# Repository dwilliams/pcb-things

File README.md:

# pcb-things
A place to keep all of the PCB things that don't fit in a project

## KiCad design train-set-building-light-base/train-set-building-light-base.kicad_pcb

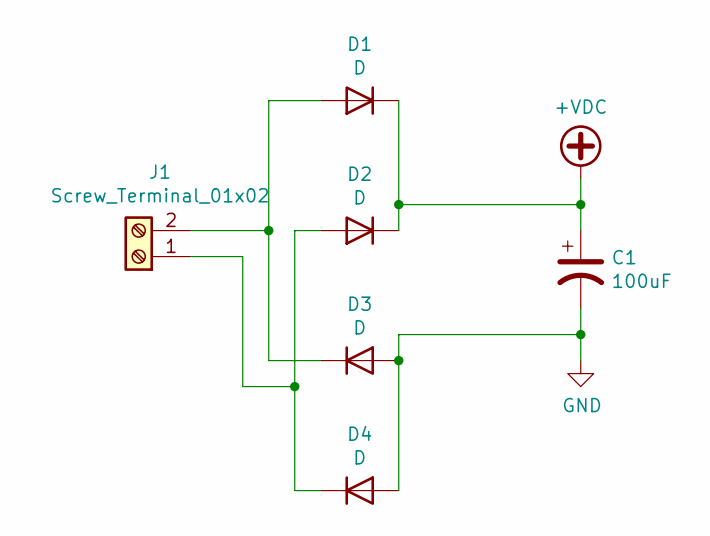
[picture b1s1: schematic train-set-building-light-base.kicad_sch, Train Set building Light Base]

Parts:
C1: 100uF; CP_Elec_8x5.4
D1, D2, D3, D4: D; D_SMA-SMB_Universal_Handsoldering
J1: Screw_Terminal_01x02; PhoenixContact_MCV_1,5_2-G-5.08_1x02_P5.08mm_Vertical

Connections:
+VDC: C1.1, D1.1 (K), D2.1 (K)
GND: C1.2, D3.2 (A), D4.2 (A)
unnamed: D1.2 (A), D3.1 (K), J1.2
unnamed: D2.2 (A), D4.1 (K), J1.1

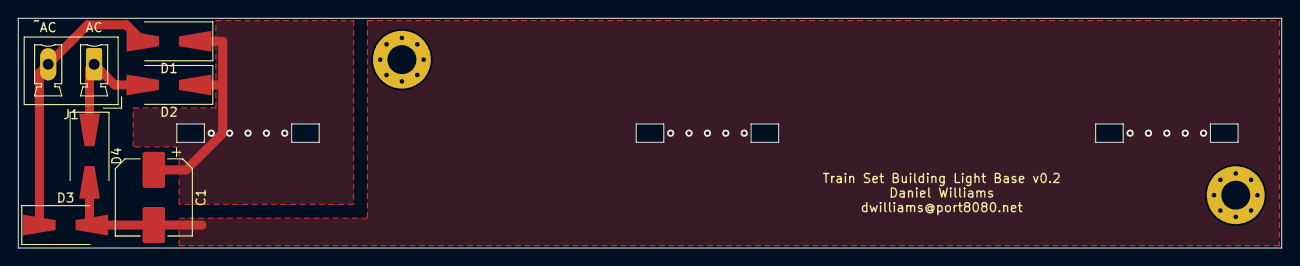
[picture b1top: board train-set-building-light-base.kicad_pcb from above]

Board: 2 copper layers, 139.7 x 25.4 mm, 6 parts (0 on the bottom side), 4 nets.

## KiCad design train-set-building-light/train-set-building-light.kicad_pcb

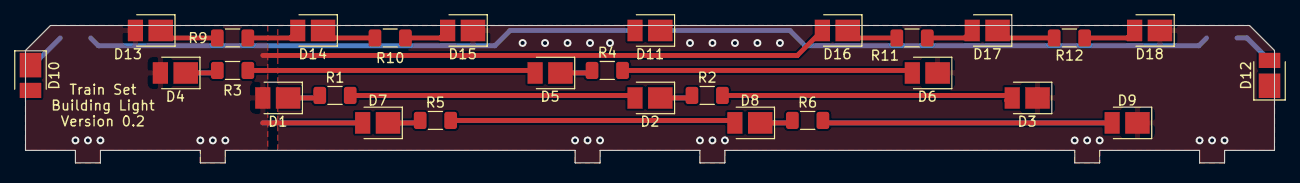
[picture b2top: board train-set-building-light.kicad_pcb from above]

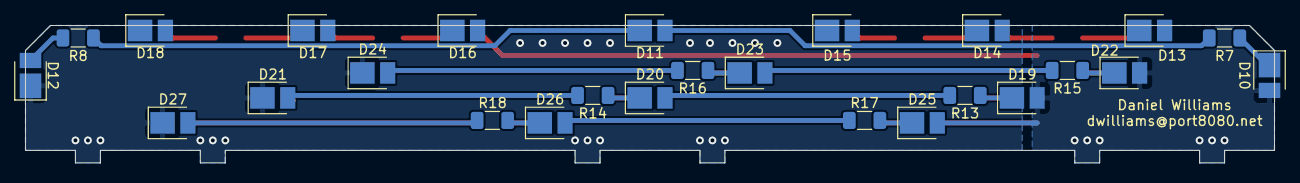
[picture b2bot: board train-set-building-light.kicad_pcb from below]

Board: 2 copper layers, 127.0 x 14.0 mm, 54 parts (26 on the bottom side), 38 nets.

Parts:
D1, D2, D3, D4, D5, D6, D7, D8, D9, D10, D10#2, D11, D11#2, D12, D12#2, D13, D13#2, D14, D14#2, D15, D15#2, D16, D16#2, D17, D17#2, D18, D18#2, D19, D20, D21, D22, D23, D24, D25, D26, D27: LED; LED_PLCC_2835_Handsoldering
R1, R2, R3, R4, R5, R6, R7, R8, R9, R10, R11, R12, R13, R14, R15, R16, R17, R18: 150; R_1206_3216Metric_Pad1.30x1.75mm_HandSolder

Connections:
+VDC: D1.2, D4.2, D7.2, D10#2.2, D13.2, D16.2, D19.2, D22.2, D25.2
GND: D3.1, D6.1, D9.1, D12#2.1, D15.1, D18.1, D21.1, D24.1, D27.1
unnamed: D1.1, R1.1
unnamed: D2.1, R2.1
unnamed: D2.2, R1.2
unnamed: D3.2, R2.2
unnamed: D4.1, R3.1
unnamed: D5.1, R4.1
unnamed: D5.2, R3.2
unnamed: D6.2, R4.2
unnamed: D7.1, R5.1
unnamed: D8.1, R6.1
unnamed: D8.2, R5.2
unnamed: D9.2, R6.2
unnamed: D10#2.1, R7.1
unnamed: D11#2.1, R8.1
unnamed: D11#2.2, R7.2
unnamed: D12#2.2, R8.2
unnamed: D13.1, R9.1
unnamed: D14.1, R10.1
unnamed: D14.2, R9.2
unnamed: D15.2, R10.2
unnamed: D16.1, R11.1
unnamed: D17.1, R12.1
unnamed: D17.2, R11.2
unnamed: D18.2, R12.2
unnamed: D19.1, R13.1
unnamed: D20.1, R14.1
unnamed: D20.2, R13.2
unnamed: D21.2, R14.2
unnamed: D22.1, R15.1
unnamed: D23.1, R16.1
unnamed: D23.2, R15.2
unnamed: D24.2, R16.2
unnamed: D25.1, R17.1
unnamed: D26.1, R18.1
unnamed: D26.2, R17.2
unnamed: D27.2, R18.2

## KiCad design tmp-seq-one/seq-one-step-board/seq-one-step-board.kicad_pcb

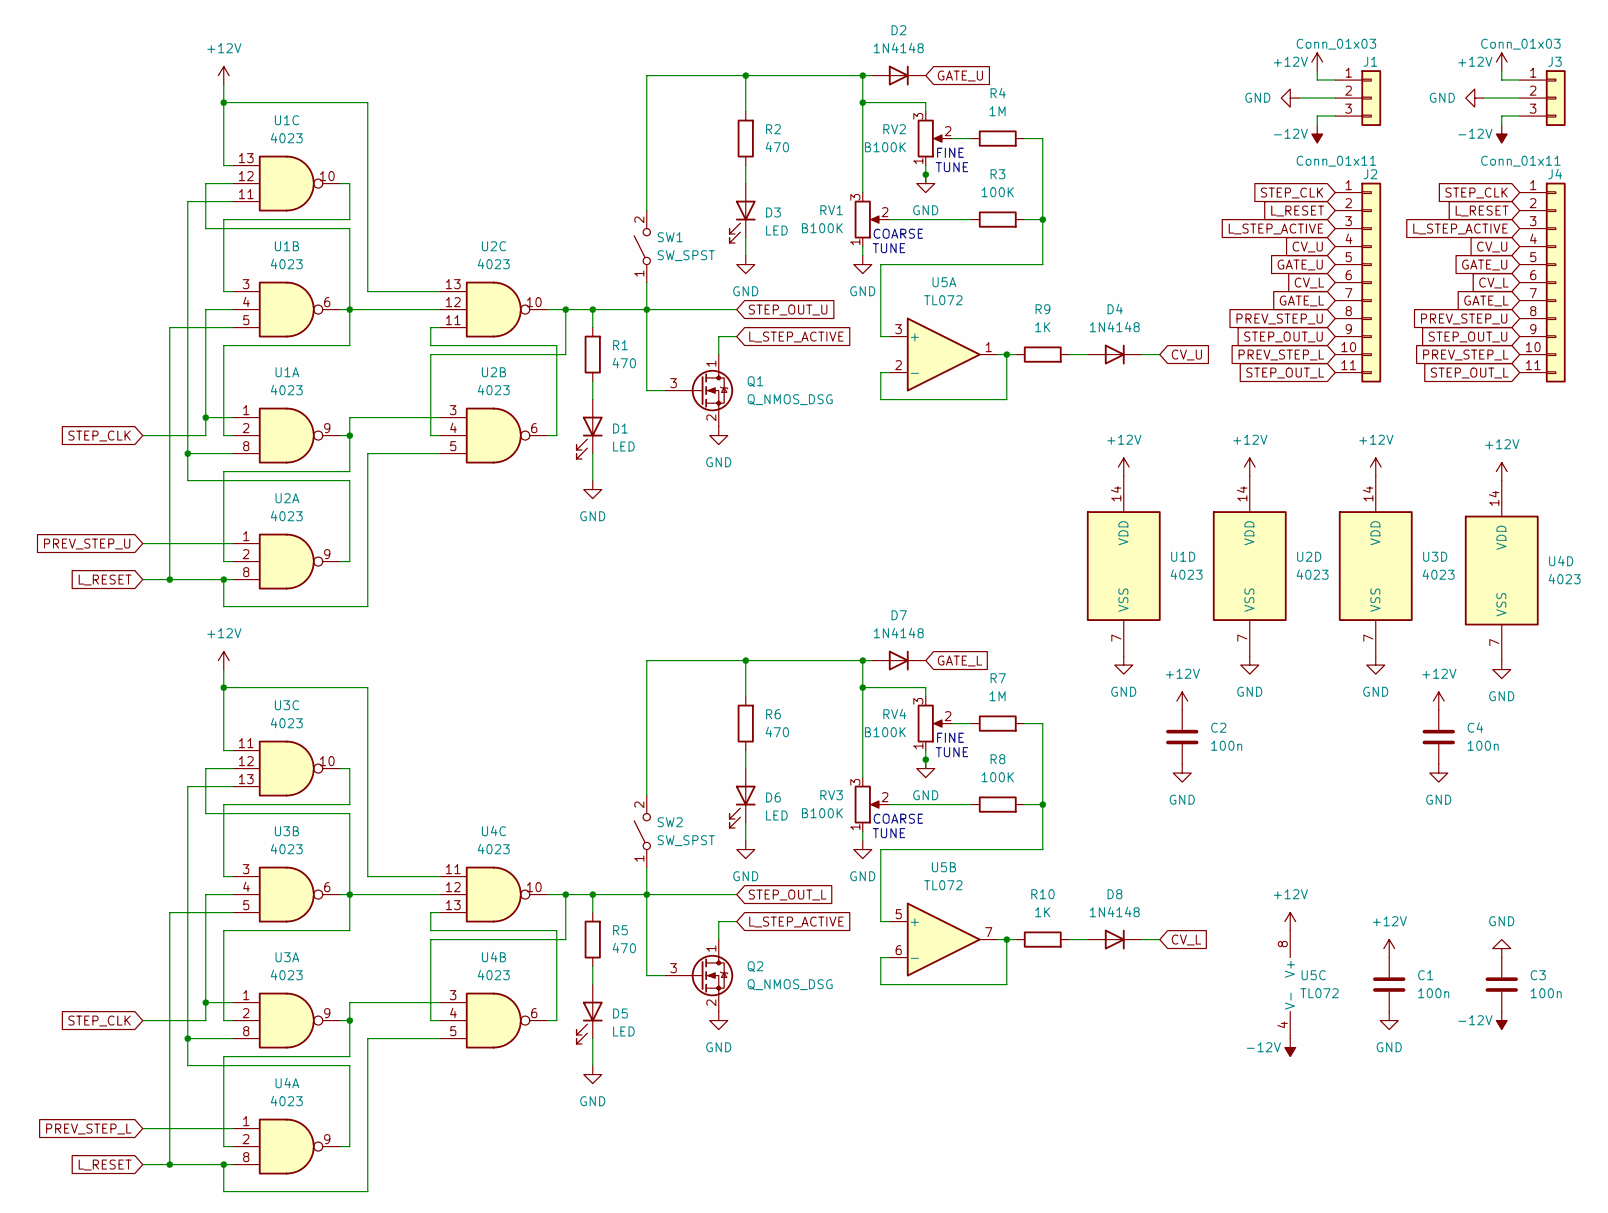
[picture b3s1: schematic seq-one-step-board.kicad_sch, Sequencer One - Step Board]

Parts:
C1, C2, C3, C4: 100n; C_Disc_D5.1mm_W3.2mm_P5.00mm
D1, D3, D5, D6: LED; LED_D3.0mm
D2, D4, D7, D8: 1N4148; D_DO-35_SOD27_P7.62mm_Horizontal
J1, J3: Conn_01x03; PinHeader_1x03_P2.54mm_Vertical
J2, J4: Conn_01x11; PinHeader_1x11_P2.54mm_Vertical
Q1, Q2: Q_NMOS_DSG; TO-92_HandSolder
R1, R2, R5, R6: 470; R_Axial_DIN0204_L3.6mm_D1.6mm_P7.62mm_Horizontal
R3, R8: 100K; R_Axial_DIN0204_L3.6mm_D1.6mm_P7.62mm_Horizontal
R4, R7: 1M; R_Axial_DIN0204_L3.6mm_D1.6mm_P7.62mm_Horizontal
R9, R10: 1K; R_Axial_DIN0204_L3.6mm_D1.6mm_P7.62mm_Horizontal
RV1, RV2, RV3, RV4: B100K; Potentiometer_Piher_T-16H_Single_Horizontal
SW1, SW2: SW_SPST; PinHeader_1x02_P2.54mm_Vertical
U1, U2, U3, U4: 4023; DIP-14_W7.62mm_Socket_LongPads
U5: TL072; DIP-8_W7.62mm_Socket_LongPads

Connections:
+12V: C1.1, C2.1, C4.1, J1.1, J3.1, U1.13, U1.14 (VDD), U2.13, U2.14 (VDD), U3.11, U3.14 (VDD), U4.11, U4.14 (VDD), U5.8 (V+)
-12V: C3.2, J1.3, J3.3, U5.4 (V-)
CV_L: D8.1 (K), J2.6, J4.6
CV_U: D4.1 (K), J2.4, J4.4
GATE_L: D7.1 (K), J2.7, J4.7
GATE_U: D2.1 (K), J2.5, J4.5
GND: C1.2, C2.2, C3.1, C4.2, D1.1 (K), D3.1 (K), D5.1 (K), D6.1 (K), J1.2, J3.2, Q1.2 (S), Q2.2 (S), RV1.1, RV2.1, RV3.1, RV4.1, U1.7 (VSS), U2.7 (VSS), U3.7 (VSS), U4.7 (VSS)
L_RESET: J2.2, J4.2, U1.5, U2.5, U2.8, U3.5, U4.5, U4.8
L_STEP_ACTIVE: J2.3, J4.3, Q1.1 (D), Q2.1 (D)
unnamed: D1.2 (A), R1.1
unnamed: D2.2 (A), R2.2, RV1.3, RV2.3, SW1.2 (B)
unnamed: D3.2 (A), R2.1
unnamed: D4.2 (A), R9.2
unnamed: D5.2 (A), R5.1
unnamed: D6.2 (A), R6.1
unnamed: D7.2 (A), R6.2, RV3.3, RV4.3, SW2.2 (B)
unnamed: D8.2 (A), R10.2
unnamed: R3.1, RV1.2
unnamed: R3.2, R4.2, U5.3 (+)
unnamed: R4.1, RV2.2
unnamed: R7.1, RV4.2
unnamed: R7.2, R8.2, U5.5 (+)
unnamed: R8.1, RV3.2
unnamed: R9.1, U5.1, U5.2 (-)
unnamed: R10.1, U5.6 (-), U5.7
unnamed: U1.9, U2.2, U2.3
unnamed: U1.3, U1.10
unnamed: U1.8, U1.11, U2.9
unnamed: U1.2, U1.6, U1.12, U2.12
unnamed: U2.6, U2.11
unnamed: U3.9, U4.2, U4.3
unnamed: U3.3, U3.10
unnamed: U3.2, U3.6, U3.12, U4.12
unnamed: U3.8, U3.13, U4.9
unnamed: U4.6, U4.13
PREV_STEP_L: J2.10, J4.10, U4.1
PREV_STEP_U: J2.8, J4.8, U2.1
STEP_CLK: J2.1, J4.1, U1.1, U1.4, U3.1, U3.4
STEP_OUT_L: J2.11, J4.11, Q2.3 (G), R5.2, SW2.1 (A), U4.4, U4.10
STEP_OUT_U: J2.9, J4.9, Q1.3 (G), R1.2, SW1.1 (A), U2.4, U2.10

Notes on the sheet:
COARSE TUNE
FINE TUNE

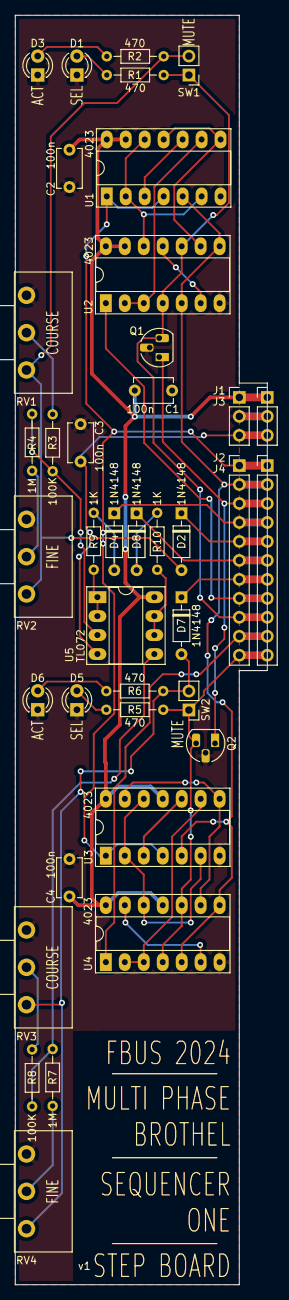
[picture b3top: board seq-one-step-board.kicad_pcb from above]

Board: 2 copper layers, 33.8 x 170.0 mm, 39 parts (0 on the bottom side), 40 nets.

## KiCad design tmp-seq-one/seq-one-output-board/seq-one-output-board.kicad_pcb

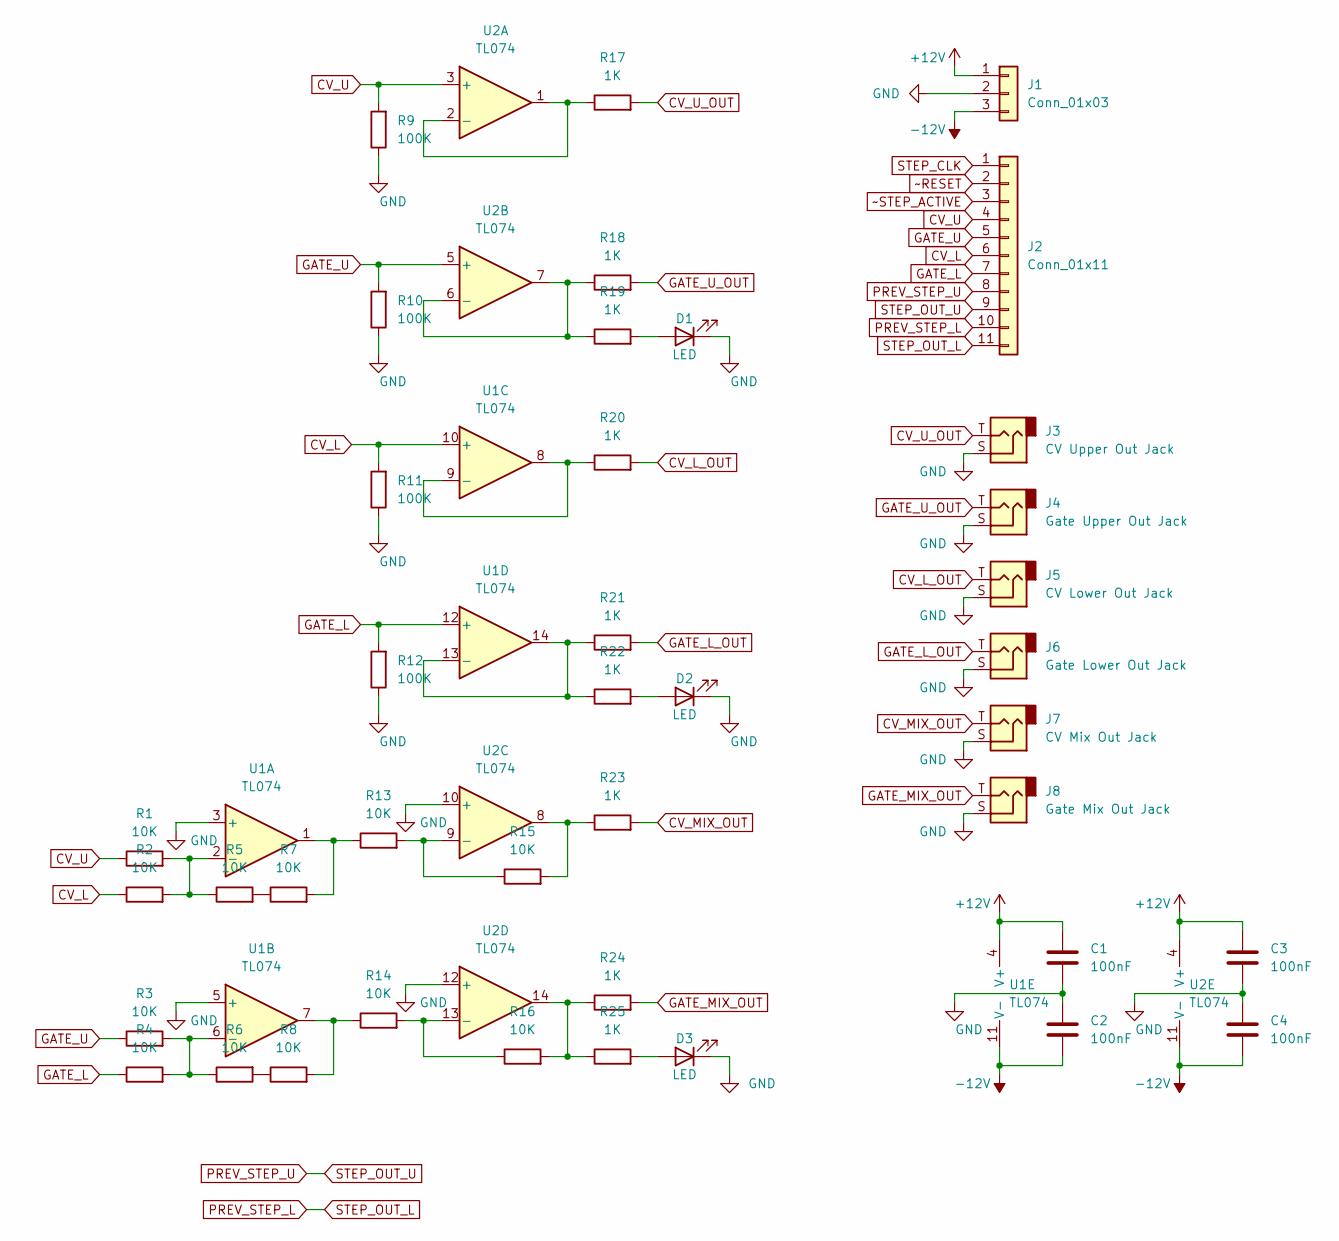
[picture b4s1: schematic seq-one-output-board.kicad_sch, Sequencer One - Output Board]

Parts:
C1, C2, C3, C4: 100nF; C_Disc_D5.1mm_W3.2mm_P5.00mm
D1, D2, D3: LED; LED_D5.0mm
J1: Conn_01x03; PinHeader_1x03_P2.54mm_Vertical
J2: Conn_01x11; PinHeader_1x11_P2.54mm_Vertical
J3: CV Upper Out Jack; Jack_6.35mm_Neutrik_NRJ6HM-1-PRE_Horizontal
J4: Gate Upper Out Jack; Jack_6.35mm_Neutrik_NRJ6HM-1-PRE_Horizontal
J5: CV Lower Out Jack; Jack_6.35mm_Neutrik_NRJ6HM-1-PRE_Horizontal
J6: Gate Lower Out Jack; Jack_6.35mm_Neutrik_NRJ6HM-1-PRE_Horizontal
J7: CV Mix Out Jack; Jack_6.35mm_Neutrik_NRJ6HM-1-PRE_Horizontal
J8: Gate Mix Out Jack; Jack_6.35mm_Neutrik_NRJ6HM-1-PRE_Horizontal
R1, R2, R3, R4, R5, R6, R7, R8, R13, R14, R15, R16: 10K; R_Axial_DIN0204_L3.6mm_D1.6mm_P7.62mm_Horizontal
R9, R10, R11, R12: 100K; R_Axial_DIN0204_L3.6mm_D1.6mm_P7.62mm_Horizontal
R17, R18, R19, R20, R21, R22, R23, R24, R25: 1K; R_Axial_DIN0204_L3.6mm_D1.6mm_P7.62mm_Horizontal
U1, U2: TL074; DIP-14_W7.62mm_Socket_LongPads

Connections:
+12V: C1.1, C3.1, J1.1, U1.4 (V+), U2.4 (V+)
-12V: C2.2, C4.2, J1.3, U1.11 (V-), U2.11 (V-)
CV_L: J2.6, R2.1, R11.2, U1.10 (+)
CV_L_OUT: J5.T, R20.2
CV_MIX_OUT: J7.T, R23.2
CV_U: J2.4, R1.1, R9.2, U2.3 (+)
CV_U_OUT: J3.T, R17.2
GATE_L: J2.7, R4.1, R12.2, U1.12 (+)
GATE_L_OUT: J6.T, R21.2
GATE_MIX_OUT: J8.T, R24.2
GATE_U: J2.5, R3.1, R10.2, U2.5 (+)
GATE_U_OUT: J4.T, R18.2
GND: C1.2, C2.1, C3.2, C4.1, D1.1 (K), D2.1 (K), D3.1 (K), J1.2, J3.S, J4.S, J5.S, J6.S, J7.S, J8.S, R9.1, R10.1, R11.1, R12.1, U1.3 (+), U1.5 (+), U2.10 (+), U2.12 (+)
unnamed: D1.2 (A), R19.2
unnamed: D2.2 (A), R22.2
unnamed: D3.2 (A), R25.2
unnamed: R1.2, R2.2, R5.1, U1.2 (-)
unnamed: R3.2, R4.2, R6.1, U1.6 (-)
unnamed: R5.2, R7.1
unnamed: R6.2, R8.1
unnamed: R7.2, R13.1, U1.1
unnamed: R13.2, R15.1, U2.9 (-)
unnamed: R8.2, R14.1, U1.7
unnamed: R14.2, R16.1, U2.13 (-)
unnamed: R15.2, R23.1, U2.8
unnamed: R16.2, R24.1, R25.1, U2.14
unnamed: R17.1, U2.1, U2.2 (-)
unnamed: R18.1, R19.1, U2.6 (-), U2.7
unnamed: R20.1, U1.8, U1.9 (-)
unnamed: R21.1, R22.1, U1.13 (-), U1.14
PREV_STEP_L: J2.10, J2.11
PREV_STEP_U: J2.8, J2.9
STEP_CLK: J2.1
~RESET: J2.2
~STEP_ACTIVE: J2.3

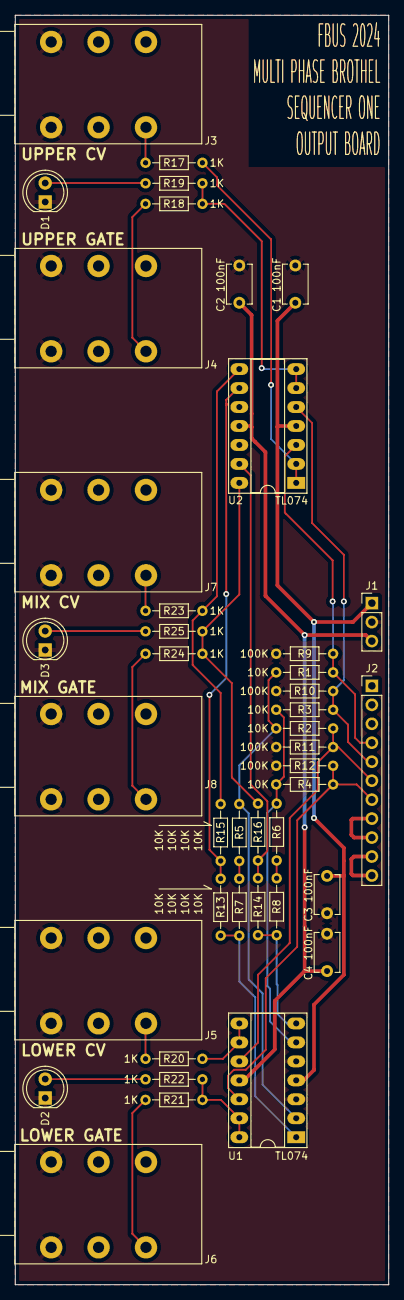
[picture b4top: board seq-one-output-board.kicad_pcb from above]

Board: 2 copper layers, 50.0 x 170.0 mm, 42 parts (0 on the bottom side), 32 nets.

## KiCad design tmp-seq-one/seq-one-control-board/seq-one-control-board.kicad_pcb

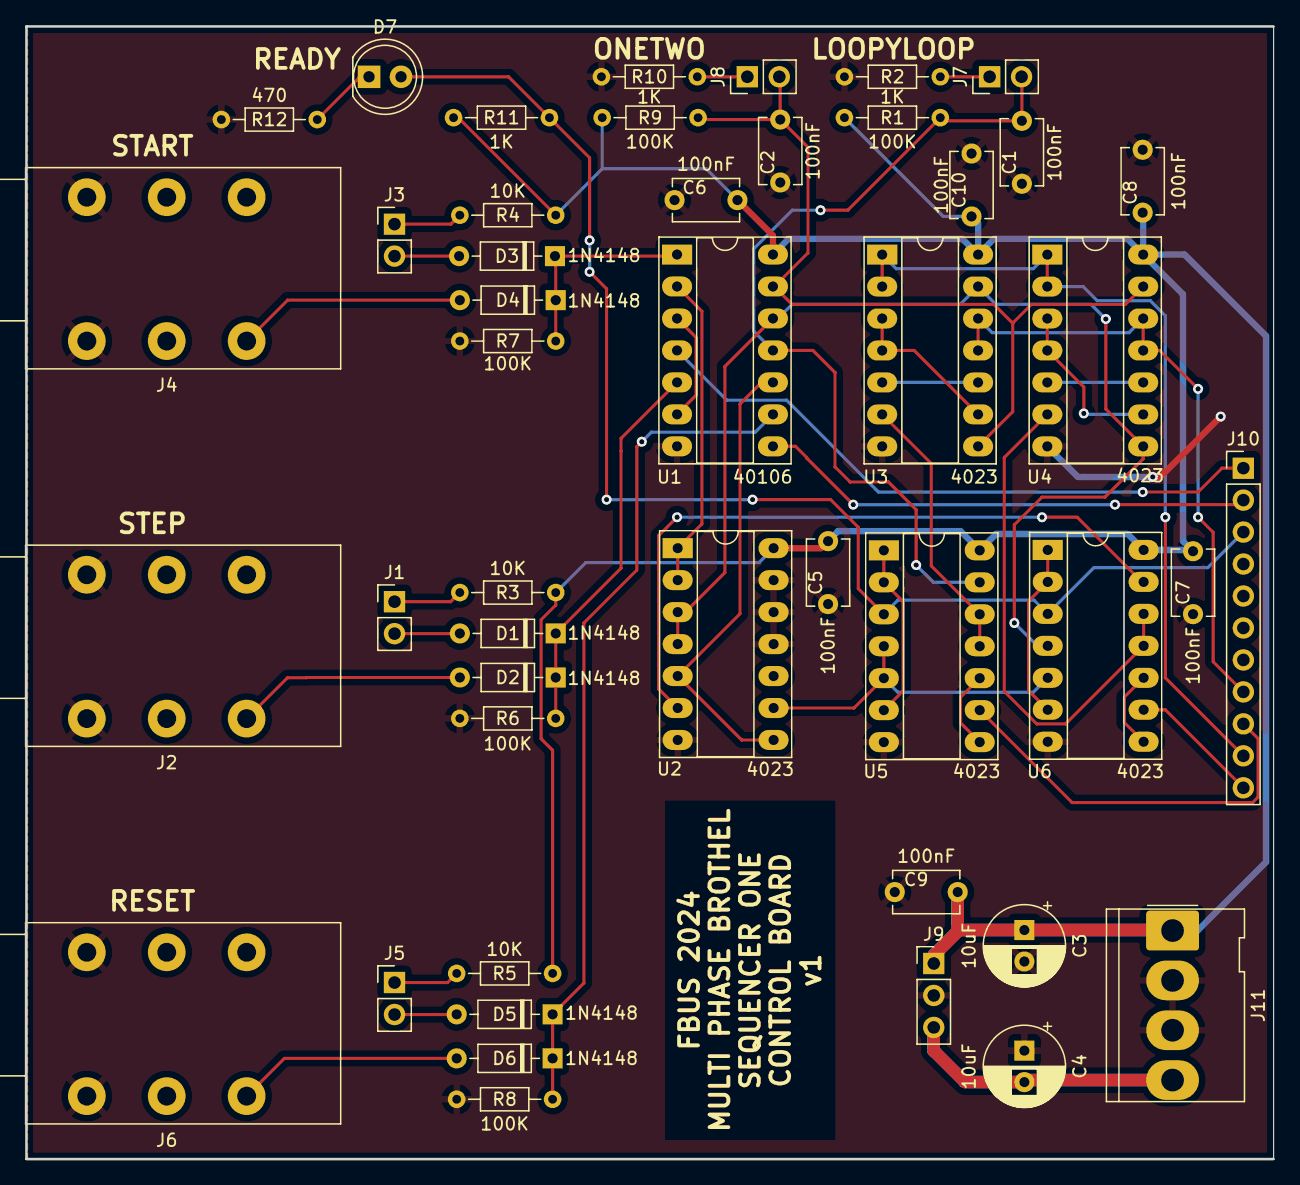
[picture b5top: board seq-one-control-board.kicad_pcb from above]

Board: 2 copper layers, 99.1 x 90.0 mm, 46 parts (0 on the bottom side), 43 nets.

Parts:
C1, C2, C5, C6, C7, C8, C9, C10: 100nF; C_Disc_D5.1mm_W3.2mm_P5.00mm
C3, C4: 10uF; CP_Radial_D6.3mm_P2.50mm
D1, D2, D3, D4, D5, D6: 1N4148; D_DO-35_SOD27_P7.62mm_Horizontal
D7: LED; LED_D5.0mm
J1: Step Button; PinHeader_1x02_P2.54mm_Vertical
J2: Step Jack; Jack_6.35mm_Neutrik_NRJ6HM-1-PRE_Horizontal
J3: Start Button; PinHeader_1x02_P2.54mm_Vertical
J4: Start Jack; Jack_6.35mm_Neutrik_NRJ6HM-1-PRE_Horizontal
J5: Reset Button; PinHeader_1x02_P2.54mm_Vertical
J6: Reset Jack; Jack_6.35mm_Neutrik_NRJ6HM-1-PRE_Horizontal
J7: Loop Switch; PinHeader_1x02_P2.54mm_Vertical
J8: OneTwo Switch; PinHeader_1x02_P2.54mm_Vertical
J9: Power to Steps; PinHeader_1x03_P2.54mm_Vertical
J10: Signals; PinHeader_1x11_P2.54mm_Vertical
J11: Power; Molex_KK-396_5273-04A_1x04_P3.96mm_Vertical
R1, R6, R7, R8, R9: 100K; R_Axial_DIN0204_L3.6mm_D1.6mm_P7.62mm_Horizontal
R2, R10, R11: 1K; R_Axial_DIN0204_L3.6mm_D1.6mm_P7.62mm_Horizontal
R3, R4, R5: 10K; R_Axial_DIN0204_L3.6mm_D1.6mm_P7.62mm_Horizontal
R12: 470; R_Axial_DIN0204_L3.6mm_D1.6mm_P7.62mm_Horizontal
U1: 40106; DIP-14_W7.62mm_Socket_LongPads
U2, U3, U4, U5, U6: 4023; DIP-14_W7.62mm_Socket_LongPads

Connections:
+12V: C3.1, C5.1, C6.1, C7.1, C8.1, C9.1, C10.1, J9.1, J11.1, R1.1, R3.1, R4.1, R5.1, R9.1, R11.1, U1.14 (VDD), U2.14 (VDD), U3.14 (VDD), U4.14 (VDD), U5.14 (VDD), U6.14 (VDD)
-12V: C4.2, J9.3, J11.4
/ATRIG: U2.9, U5.4, U5.5, U6.5
/LOOPYLOOP: C1.1, J7.2, R1.2, U1.11, U5.13
/ONETWO: C2.1, J8.2, R9.2, U1.13, U3.8, U4.13
/PICKBOTTOM: U4.6, U6.11, U6.12
/PICKTOP: U3.6, U5.11, U5.12
/RESET: D5.1 (K), D6.1 (K), R8.1, U1.9
/START: D3.1 (K), D4.1 (K), R7.1, U1.1
/TOP2BOTTOM: U2.6, U6.13
/~LOOPYLOOP: U1.10, U2.5, U2.8
/~ONETWO: U1.12, U2.3, U2.4, U3.13, U4.8, U6.4
/~START: U1.2, U2.1, U2.2
GND: C1.2, C2.2, C3.2, C4.1, C5.2, C6.2, C7.2, C8.2, C9.2, C10.2, J2.S, J4.S, J6.S, J9.2, J11.2, J11.3, R2.2, R6.2, R7.2, R8.2, R10.2, R12.2, U1.7 (VSS), U2.7 (VSS), U2.11, U2.12, U2.13, U3.7 (VSS), U4.7 (VSS), U5.7 (VSS), U6.7 (VSS)
LOWER_PREV_STEP: J10.10, U3.1, U3.2, U4.1, U4.2
LOWER_STEP_OUT: J10.11, U6.9
unnamed: D1.1 (K), D2.1 (K), R6.1, U1.5
unnamed: D1.2 (A), J1.2
unnamed: D2.2 (A), J2.T
unnamed: D3.2 (A), J3.2
unnamed: D4.2 (A), J4.T
unnamed: D5.2 (A), J5.2
unnamed: D6.2 (A), J6.T
unnamed: D7.1 (K), R12.1
unnamed: J1.1, R3.2
unnamed: J3.1, R4.2
unnamed: J5.1, R5.2
unnamed: J7.1, R2.1
unnamed: J8.1, R10.1
unnamed: U1.3, U1.6
unnamed: U3.3, U3.4, U3.9
unnamed: U3.5, U3.10
unnamed: U4.3, U4.4, U4.9
unnamed: U4.5, U4.10
unnamed: U5.1, U5.2, U5.6
unnamed: U5.8, U5.10
unnamed: U6.1, U6.2, U6.6
unnamed: U6.8, U6.10
STEP_CLK: J10.1, U1.4
UPPER_PREV_STEP: J10.8, U3.11, U3.12, U4.11, U4.12
UPPER_STEP_OUT: J10.9, U5.9
~RESET: J10.2, U1.8
~STEP_ACTIVE: D7.2 (A), J10.3, R11.2, U5.3, U6.3

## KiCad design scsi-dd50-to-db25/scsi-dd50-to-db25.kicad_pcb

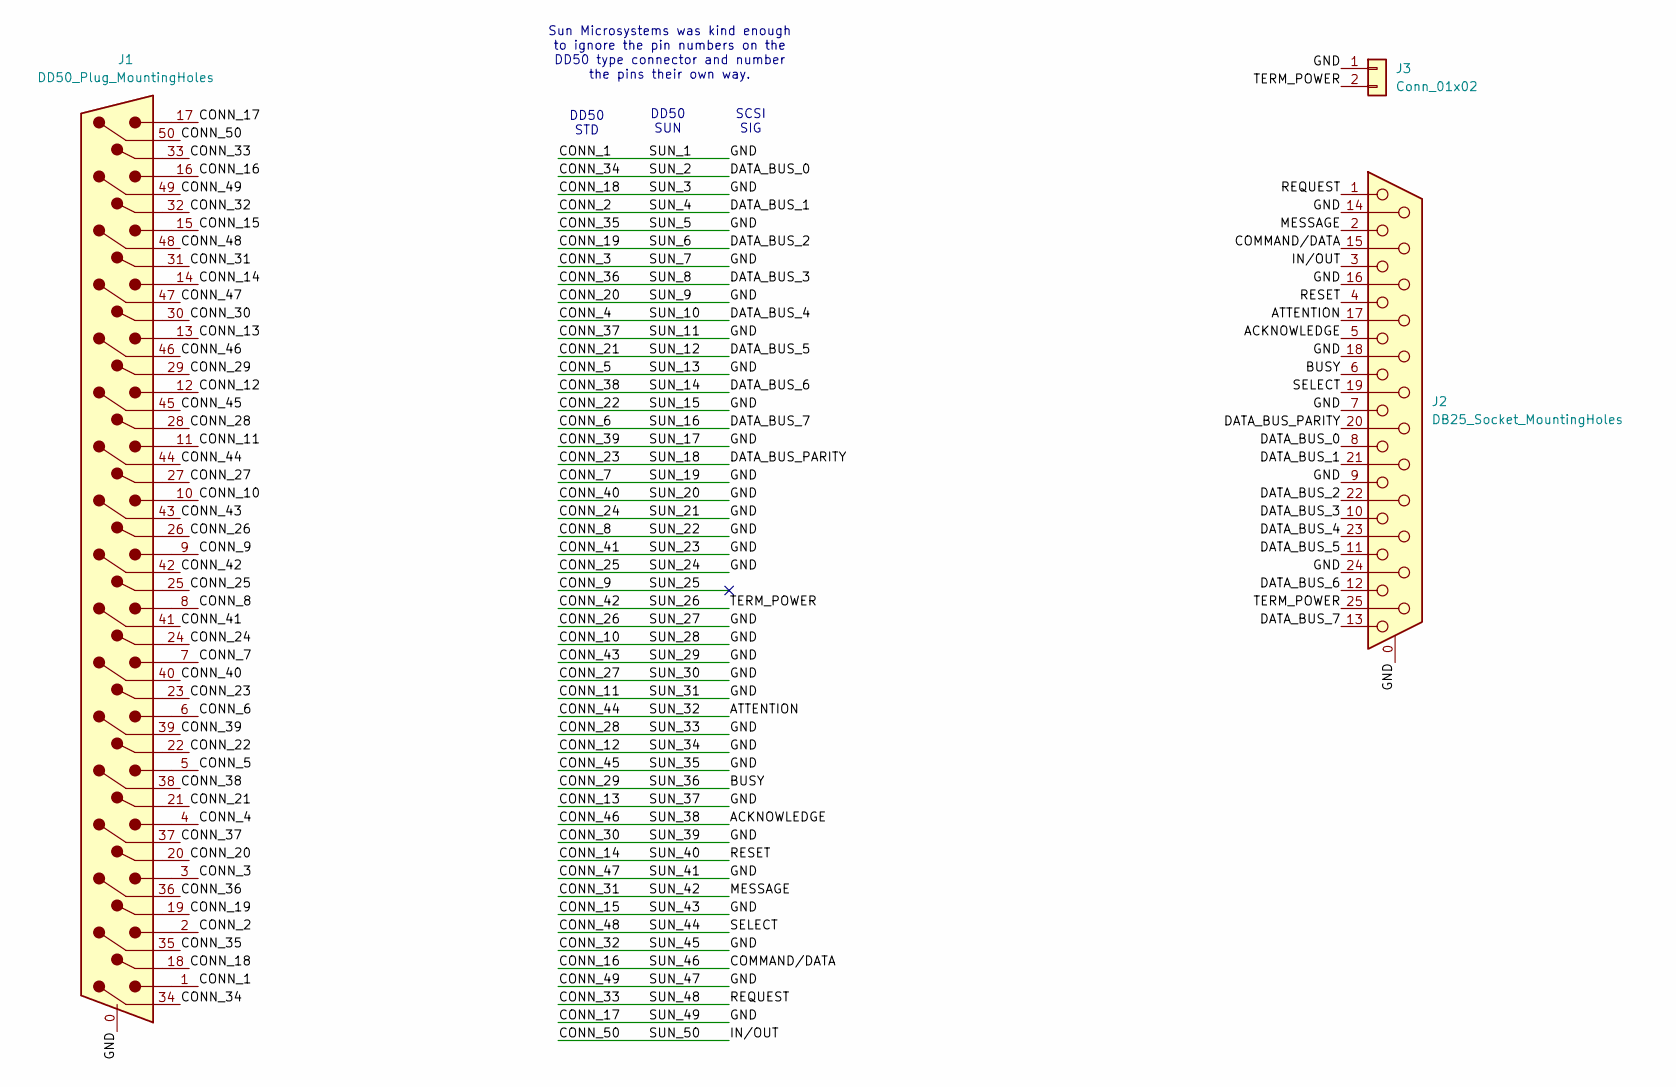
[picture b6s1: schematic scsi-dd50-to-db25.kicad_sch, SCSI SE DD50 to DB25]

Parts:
J1: DD50_Plug_MountingHoles; DSUB-50_Male_Horizontal_P2.76x2.84mm_EdgePinOffset10.40mm_H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
J2: DB25_Socket_MountingHoles; DSUB-25_Socket_Horizontal_P2.77x2.84mm_EdgePinOffset9.90mm_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
J3: Conn_01x02; PinHeader_1x02_P2.54mm_Horizontal

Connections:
/ACKNOWLEDGE: J1.46, J2.5
/ATTENTION: J1.44, J2.17
/BUSY: J1.29, J2.6
/COMMAND/DATA: J1.16, J2.15
/CONN_1: J1.0, J1.1, J1.3, J1.5, J1.7, J1.8, J1.10, J1.11, J1.12, J1.13, J1.15, J1.17, J1.18, J1.20, J1.22, J1.24, J1.25, J1.26, J1.27, J1.28, J1.30, J1.32, J1.35, J1.37, J1.39, J1.40, J1.41, J1.43, J1.45, J1.47, J1.49, J2.0 (PAD), J2.7, J2.9, J2.14, J2.16, J2.18, J2.24, J3.1
/CONN_2: J1.2, J2.21
/CONN_4: J1.4, J2.23
/CONN_6: J1.6, J2.13
/CONN_9: J1.9
/CONN_14: J1.14, J2.4
/CONN_19: J1.19, J2.22
/CONN_21: J1.21, J2.11
/CONN_23: J1.23, J2.20
/CONN_31: J1.31, J2.2
/CONN_33: J1.33, J2.1
/CONN_34: J1.34, J2.8
/CONN_36: J1.36, J2.10
/CONN_38: J1.38, J2.12
/CONN_42: J1.42, J2.25, J3.2
/CONN_48: J1.48, J2.19
/CONN_50: J1.50, J2.3

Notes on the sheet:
Sun Microsystems was kind enough to ignore the pin numbers on the DD50 type connector and number the pins their own way.
SCSI SIG
DD50 SUN
DD50 STD

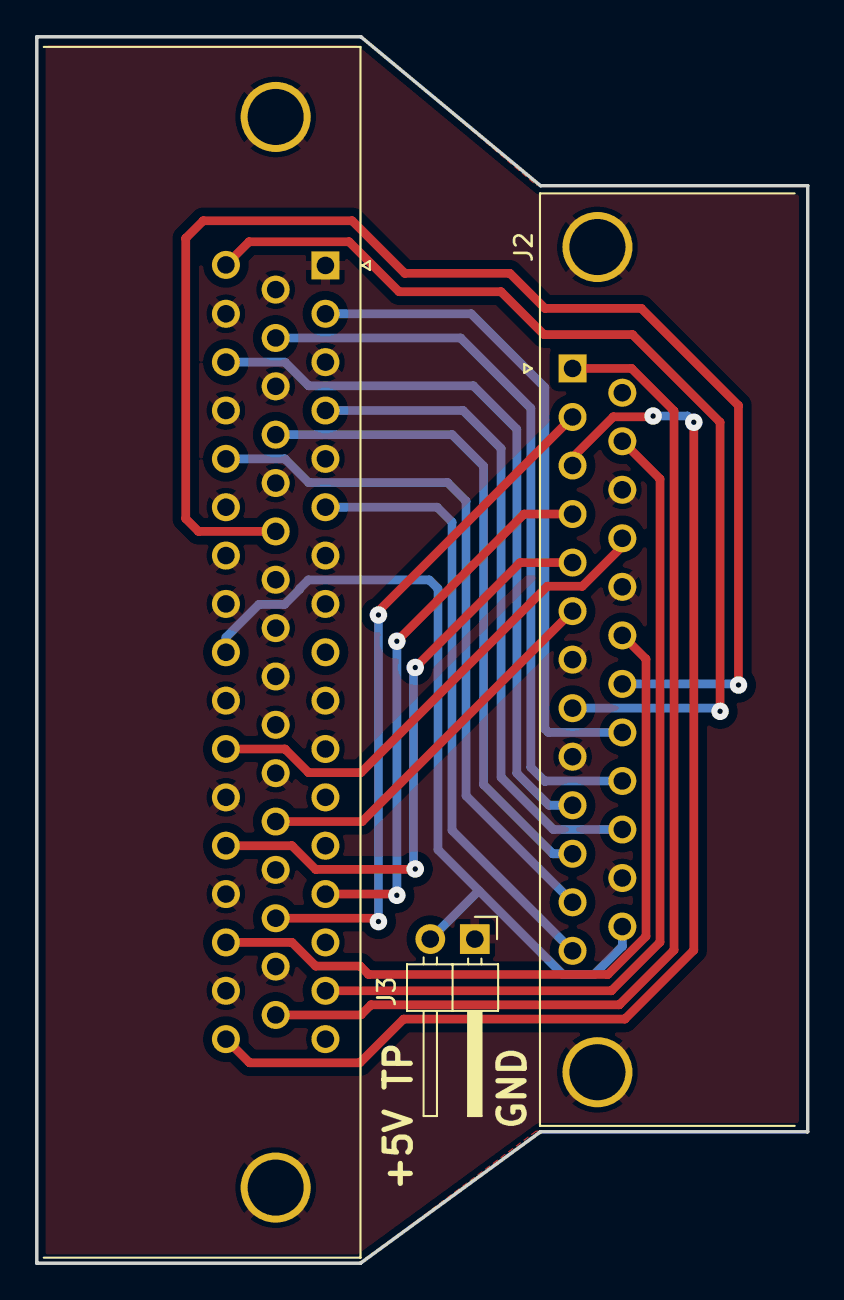
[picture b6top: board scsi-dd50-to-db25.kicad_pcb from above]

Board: 2 copper layers, 44.0 x 70.0 mm, 3 parts (0 on the bottom side), 20 nets.

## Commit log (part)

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2019-10-09 Adding a board to act as a panel for an octal tube socket.
2019-10-09 Moved the mounting screws to support two types of socket.
2019-10-09 Adding a noval base panel.
2020-10-26 Adding a plinth PCB for a B7A type tube base.
2020-10-26 Adding a footprint for the RECOM type RAC04-C/230 type modules.
2021-01-08 Adding a couple of pcbs for a light for inside buildings in a train set. Also adding a couple of libraries.
2021-01-08 Added a couple items to the gitignore file.
2022-09-16 Adding a bunch of projects.
2022-11-15 Adding a simple power distribution board for the modular synth.
2022-11-15 Fixing a small issue with missing solder masks.
2023-08-16 Adding a few PCBs for tube test fixtures.
2024-07-19 Committing here for now. Should move over to MPB
2025-03-04 Adding the SCSI DD50 to DB25 board.
2025-03-05 Added a term power port for pulling 5v off to another adapter.
2025-03-12 Fixing the pinout of the Sun Microsystems SCSI SE DD50 connector.
2026-02-09 Updating to KiCad 9.0
2026-02-09 Updating KiCad Libs
2026-02-09 Adding the start of a project to use the little TV speakers that I bought an entire box of.
